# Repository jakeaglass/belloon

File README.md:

##Belloon &ndash; Bellarmine College Prep's High Altitude Balloon Project &ndash; Code, Schematics, and PCB Layout

Launching in ~~winter~~ summer of 2016 (targeting ~~January~~ June) to ~35km of altitude with a 1600g Hydrogen-filled latex balloon and a sensor package complete with the following:

- Camera (GoPro HERO))
- 144.390MHz APRS RadioMetrix Radio for telemetry
- GPS tracker (model TBD)
- ATMega CPU (with Arduino bootloader) with SD card for data logging
- Gas sensors (a sensor that can detect carbon-based gases and nitrous oxide, some of the worse pollutants in the atmosphere that also cause smog)
- Humidity Sensor
- Temperature Sensor

Once the balloon's payload&mdash;the board and sensors&mdash;is complete, we'll be able to launch and make use of the data collected to study environmental changes in the Earth’s atmosphere. Launch will be carried out with the help of the California Near Space Project, which has volunteered to facilitate the launch and retrieval. 

The board design is complete as of May 12 and has been sent off to be fabricated, so it will be debugged in person shortly. See the updated files for the full schematic and board (both done in EAGLE), gerber files, and BOM.

 &ndash; [Jake Glass](http://jake.glass) & [Mihir Trivedi](http://mihirtrivedi.com/)

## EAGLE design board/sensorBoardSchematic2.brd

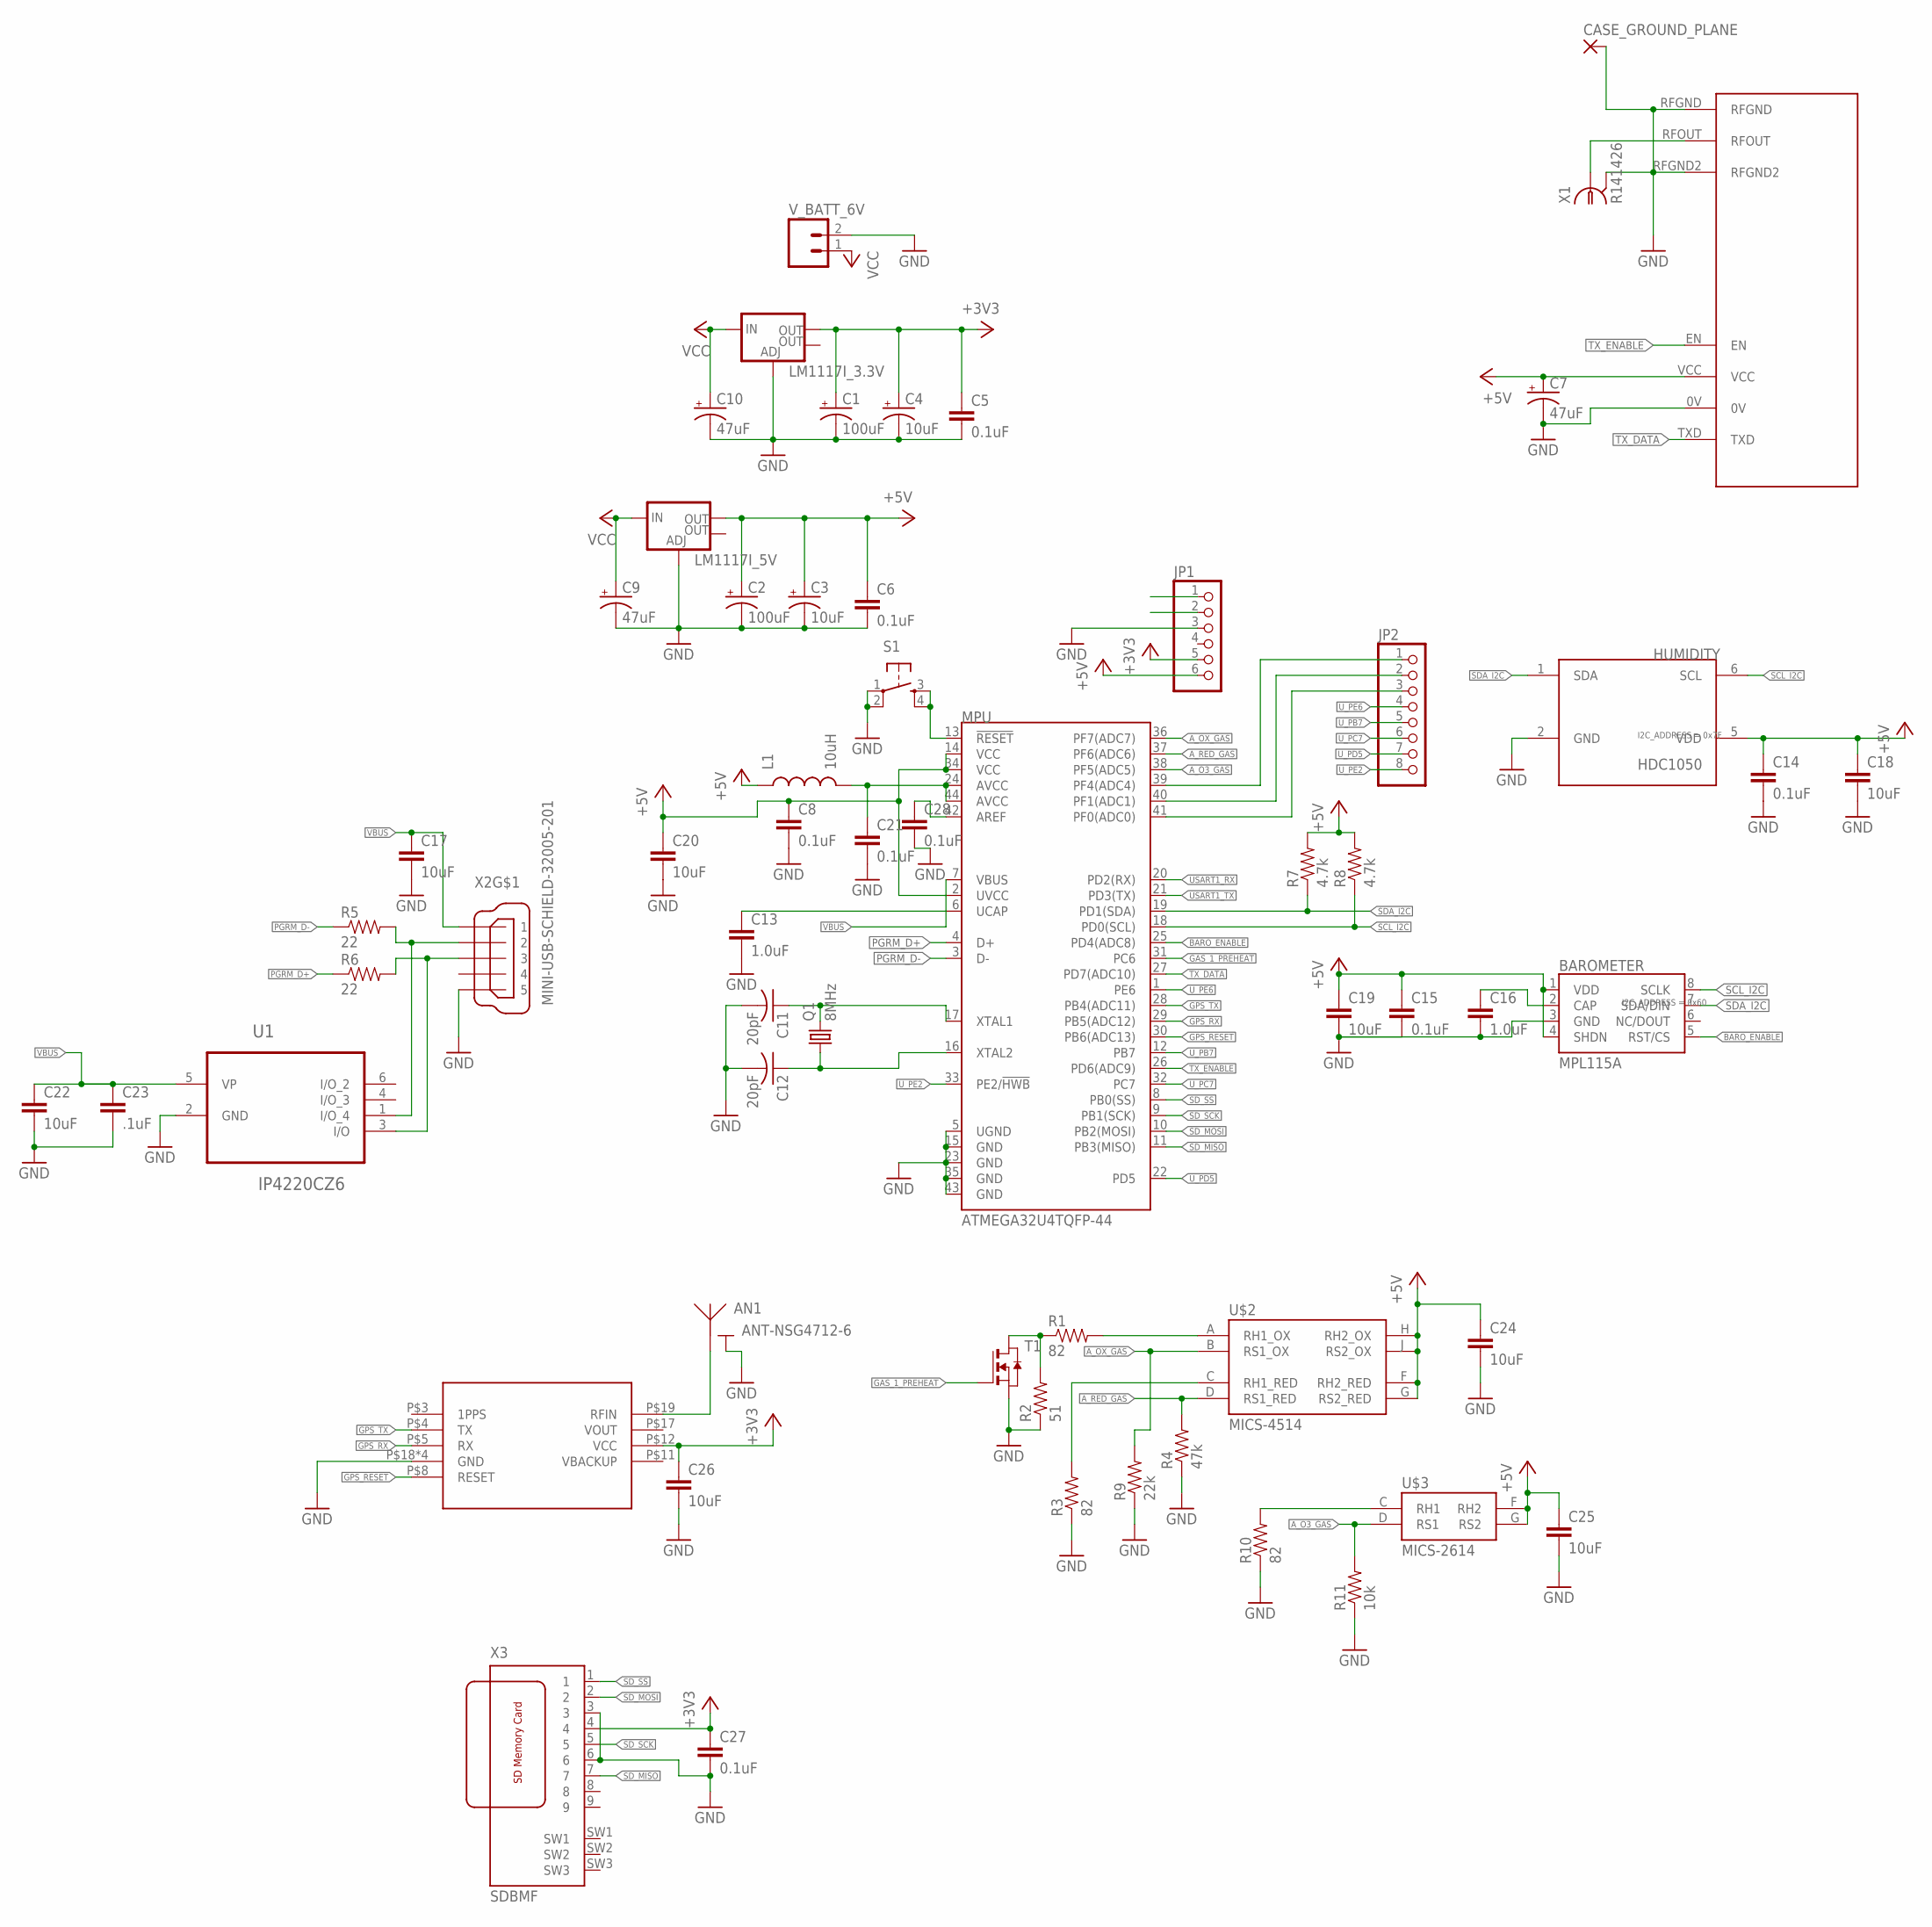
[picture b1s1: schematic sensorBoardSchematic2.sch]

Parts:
AN1: ANT-NSG4712-6
BAROMETER: MPL115A; LGA8
C1, C2: 100uF; EIA7343
C3, C4: 10uF; EIA3216
C5, C6, C27: 0.1uF; 0402-CAP
C7, C9, C10: 47uF; EIA3528
C8, C14, C15, C21, C28: 0.1uF; 0603-CAP
C11, C12: 20pF; C0402
C13, C16: 1.0uF; 0603-CAP
C17, C18, C19, C20, C22, C24, C25, C26: 10uF; 0603-CAP
C23: .1uF; 0603-CAP
CASE_GROUND_PLANE: 3,81/1,4
HUMIDITY: HDC1050; TI-S-PWSON-N6
IC1: RXM-GPS-FM; SMD-22
JP1: PINHD-1X6; 1X06
JP2: PINHD-1X8; 1X08
L1: 10uH; 1007
LM1117I_3.3V, LM1117I_5V: V_REG_LM1117SOT223; SOT223
MPU: ATMEGA32U4TQFP-44; TQFP44
Q1: 8MHz; HC49U70
R1, R3, R10: 82; 0402-RES
R2: 51; 0402-RES
R4: 47k; 0402-RES
R5, R6: 22; 0402-RES
R7, R8: 4.7k; 0402-RES
R9: 22k; 0402-RES
R11: 10k; 0402-RES
S1: TAC_SWITCHPTH; TACTILE-PTH
T1: NMOSSOT23; SOT-23
U1: IP4220CZ6; SOT95P275X110-6N
U$1: RADIOMETRIX-HX1
U$2: MICS-4514; MICS_10-SMD
U$3: MICS-2614; MICS_10-SMD
V_BATT_6V: M025MM; SCREWTERMINAL-5MM-2
X1: R141426
X2: MINI-USB-SCHIELD-32005-201; 32005-201
X3: SDBMF; SDBMF-009XXBXX2

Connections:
+3V3: C1.A (+), C4.A (+), C5.1, C26.1, C27.1, IC1.P$12 (VCC), JP1.5, LM1117I_3.3V.2 (OUT), X3.4
+5V: BAROMETER.1 (VDD), BAROMETER.4 (SHDN), C2.A (+), C3.A (+), C6.1, C7.A (+), C8.1, C14.1, C15.1, C18.1, C19.1, C20.1, C24.1, C25.1, HUMIDITY.5 (VDD), JP1.6, L1.1, LM1117I_5V.2 (OUT), MPU.2 (UVCC), MPU.14 (VCC), MPU.34 (VCC), R7.2, R8.2, U$1.VCC, U$2.F (RH2_RED), U$2.G (RS2_RED), U$2.H (RH2_OX), U$2.J (RS2_OX), U$3.F (RH2), U$3.G (RS2)
A_O3_GAS: MPU.38 (PF5(ADC5)), R11.2, U$3.D (RS1)
A_OX_GAS: MPU.36 (PF7(ADC7)), R9.2, U$2.B (RS1_OX)
A_RED_GAS: MPU.37 (PF6(ADC6)), R4.2, U$2.D (RS1_RED)
BARO_ENABLE: BAROMETER.5 (RST/CS), MPU.25 (PD4(ADC8))
GAS_1_PREHEAT: MPU.31 (PC6), T1.3 (G)
GND: AN1.G@1 (G), AN1.G@2 (G), AN1.G@3 (G), AN1.G@4 (G), AN1.G@5 (G), AN1.G@6 (G), AN1.G@7 (G), AN1.G@8 (G), AN1.G@9 (G), AN1.G@10 (G), BAROMETER.3 (GND), C1.C (-), C2.C (-), C3.C (-), C4.C (-), C5.2, C6.2, C7.C (-), C8.2, C9.C (-), C10.C (-), C11.2, C12.2, C13.2, C14.2, C15.2, C16.2, C17.2, C18.2, C19.2, C20.2, C21.2, C22.2, C23.2, C24.2, C25.2, C26.2, C27.2, C28.2, CASE_GROUND_PLANE.1, HUMIDITY.2 (GND), IC1.P$18 (GND), IC1.P$20 (GND), IC1.P$21 (GND), IC1.P$22 (GND), JP1.3, LM1117I_3.3V.1 (ADJ), LM1117I_5V.1 (ADJ), MPU.5 (UGND), MPU.15 (GND), MPU.23 (GND), MPU.35 (GND), MPU.43 (GND), R2.1, R3.1, R4.1, R9.1, R10.1, R11.1, S1.1, S1.2, T1.2 (S), U1.2 (GND), U$1.0V, U$1.RFGND, U$1.RFGND2, V_BATT_6V.2, X1.2, X1.3 (2), X1.4 (2), X1.5 (2), X2.5, X3.3, X3.6
GPS_RESET: IC1.P$8 (RESET), MPU.30 (PB6(ADC13))
GPS_RX: IC1.P$5 (RX), MPU.29 (PB5(ADC12))
GPS_TX: IC1.P$4 (TX), MPU.28 (PB4(ADC11))
unnamed: MPU.13 (!RESET), S1.3, S1.4
unnamed: U$1.RFOUT, X1.1
unnamed: AN1.A (ANT), IC1.P$19 (RFIN)
unnamed: C21.1, L1.2, MPU.24 (AVCC), MPU.44 (AVCC)
unnamed: R1.2, U$2.A (RH1_OX)
unnamed: C11.1, MPU.17 (XTAL1), Q1.2
unnamed: BAROMETER.2 (CAP), C16.1
unnamed: C12.1, MPU.16 (XTAL2), Q1.1
unnamed: R5.2, U1.1 (I/O_4), X2.2
unnamed: R6.2, U1.3 (I/O), X2.3
unnamed: C13.1, MPU.6 (UCAP)
unnamed: R1.1, R2.2, T1.1 (D)
unnamed: JP2.1, MPU.39 (PF4(ADC4))
unnamed: R10.2, U$3.C (RH1)
unnamed: JP2.2, MPU.40 (PF1(ADC1))
unnamed: JP2.3, MPU.41 (PF0(ADC0))
unnamed: R3.2, U$2.C (RH1_RED)
unnamed: C28.1, MPU.42 (AREF)
PGRM_D+: MPU.4 (D+), R6.1
PGRM_D-: MPU.3 (D-), R5.1
SCL_I2C: BAROMETER.8 (SCLK), HUMIDITY.6 (SCL), MPU.18 (PD0(SCL)), R8.1
SDA_I2C: BAROMETER.7 (SDA/DIN), HUMIDITY.1 (SDA), MPU.19 (PD1(SDA)), R7.1
SD_MISO: MPU.11 (PB3(MISO)), X3.7
SD_MOSI: MPU.10 (PB2(MOSI)), X3.2
SD_SCK: MPU.9 (PB1(SCK)), X3.5
SD_SS: MPU.8 (PB0(SS)), X3.1
TX_DATA: MPU.27 (PD7(ADC10)), U$1.TXD
TX_ENABLE: MPU.26 (PD6(ADC9)), U$1.EN
USART1_RX: JP1.1, MPU.20 (PD2(RX))
USART1_TX: JP1.2, MPU.21 (PD3(TX))
U_PB7: JP2.5, MPU.12 (PB7)
U_PC7: JP2.6, MPU.32 (PC7)
U_PD5: JP2.7, MPU.22 (PD5)
U_PE2: JP2.8, MPU.33 (PE2/!HWB)
U_PE6: JP2.4, MPU.1 (PE6)
VBUS: C17.1, C22.1, C23.1, MPU.7 (VBUS), U1.5 (VP)
VCC: C9.A (+), C10.A (+), LM1117I_3.3V.3 (IN), LM1117I_5V.3 (IN), V_BATT_6V.1

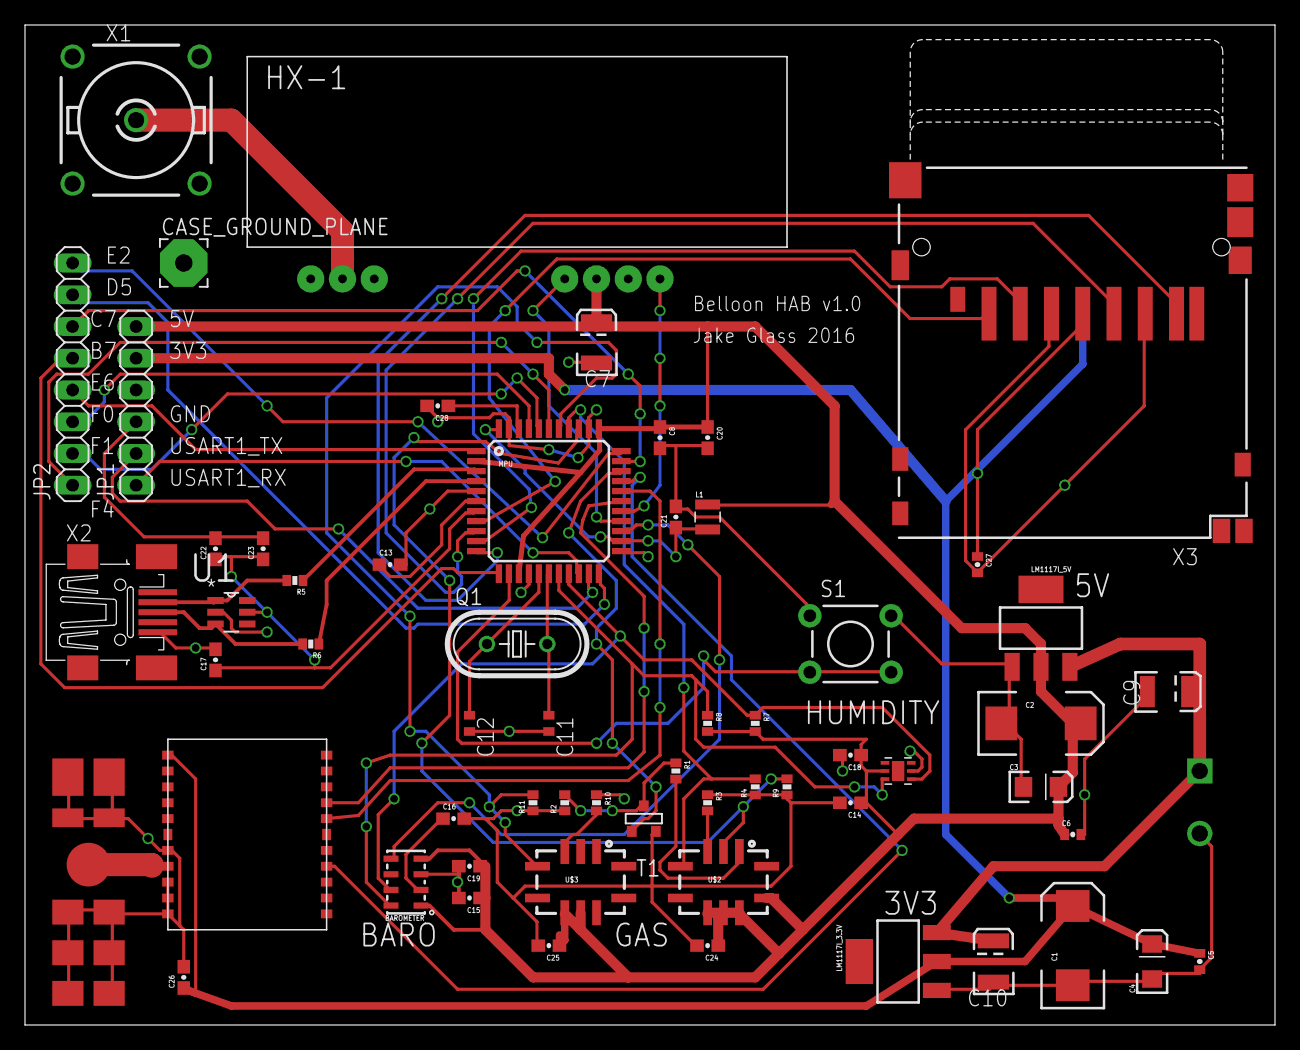
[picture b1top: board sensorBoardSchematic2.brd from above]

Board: 2 copper layers, 100.0 x 80.0 mm, 61 parts (1 on the bottom side), 48 nets.

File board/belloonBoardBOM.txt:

Partlist

Exported from sensorBoardSchematic2.brd at 5/11/2016 8:02 PM

EAGLE Version 7.5.0 Copyright (c) 1988-2015 CadSoft

Assembly variant: 

Part              Value             Package             Library                  Position (inch)       Orientation

AN1               ANT-NSG4712-6     ANT-NSG4712-6       roundsolutions           (0.2 0.45)            R0
BAROMETER         MPL115A           LGA8                SparkFun-Sensors         (1.2 0.45)            R180
C1                100uF             EIA7343             SparkFun-Capacitors      (3.3 0.25)            R90
C2                100uF             EIA7343             SparkFun-Capacitors      (3.2 0.95)            R0
C3                10uF              EIA3216             SparkFun-Retired         (3.2 0.75)            R0
C4                10uF              EIA3216             SparkFun-Retired         (3.55 0.2)            R90
C5                0.1uF             0402-CAP            SparkFun-Retired         (3.7 0.2)             R270
C6                0.1uF             0402-CAP            SparkFun-Retired         (3.3 0.6)             R0
C7                47uF              EIA3528             SparkFun-Capacitors      (1.8 2.15)            R90
C8                0.1uF             0603-CAP            SparkFun-Capacitors      (2 1.85)              R270
C9                47uF              EIA3528             SparkFun-Capacitors      (3.6 1.05)            R0
C10               47uF              EIA3528             SparkFun-Capacitors      (3.05 0.2)            R90
C11               20pF              C0402               resistor                 (1.65 0.95)           R270
C12               20pF              C0402               resistor                 (1.4 0.95)            R270
C13               1.0uF             0603-CAP            SparkFun-Capacitors      (1.15 1.45)           R0
C14               0.1uF             0603-CAP            SparkFun-Capacitors      (2.6 0.7)             R180
C15               0.1uF             0603-CAP            SparkFun-Capacitors      (1.4 0.4)             R180
C16               1.0uF             0603-CAP            SparkFun-Capacitors      (1.35 0.65)           R0
C17               10uF              0603-CAP            SparkFun-Capacitors      (0.6 1.15)            R90
C18               10uF              0603-CAP            SparkFun-Capacitors      (2.6 0.85)            R180
C19               10uF              0603-CAP            SparkFun-Capacitors      (1.4 0.5)             R180
C20               10uF              0603-CAP            SparkFun-Capacitors      (2.15 1.85)           R270
C21               0.1uF             0603-CAP            SparkFun-Capacitors      (2.05 1.6)            R90
C22               10uF              0603-CAP            SparkFun-Capacitors      (0.6 1.5)             R90
C23               .1uF              0603-CAP            SparkFun-Capacitors      (0.75 1.5)            R90
C24               10uF              0603-CAP            SparkFun-Capacitors      (2.15 0.25)           R180
C25               10uF              0603-CAP            SparkFun-Capacitors      (1.65 0.25)           R180
C26               10uF              0603-CAP            SparkFun-Capacitors      (0.5 0.15)            R90
C27               0.1uF             0402-CAP            SparkFun-Retired         (3 1.45)              R270
C28               0.1uF             0603-CAP            SparkFun-Capacitors      (1.3 1.95)            R180
CASE_GROUND_PLANE                   3,81/1,4            wirepad                  (0.5 2.4)             R0
HUMIDITY          HDC1050           TI-S-PWSON-N6       Ava                      (2.75 0.8)            R90
IC1               RXM-GPS-FM        SMD-22              linx-addl                (0.95 0.6)            R270
JP1                                 1X06                pinhead                  (0.35 1.95)           R90
JP2                                 1X08                pinhead                  (0.15 2.05)           R90
L1                10uH              1007                SparkFun-Passives        (2.15 1.6)            R0
LM1117I_3.3V                        SOT223              SparkFun-PowerIC         (2.75 0.2)            R90
LM1117I_5V                          SOT223              SparkFun-PowerIC         (3.2 1.25)            R0
MPU               ATMEGA32U4TQFP-44 TQFP44              SparkFun-DigitalIC       (1.65 1.65)           R0
Q1                8MHz              HC49U70             crystal                  (1.55 1.2)            R0
R1                82                0402-RES            SparkFun-Passives        (2.05 0.8)            R270
R2                51                0402-RES            SparkFun-Passives        (1.7 0.7)             R90
R3                82                0402-RES            SparkFun-Passives        (2.15 0.7)            R270
R4                47k               0402-RES            SparkFun-Passives        (2.3 0.75)            R90
R5                22                0402-RES            SparkFun-Passives        (0.85 1.4)            R180
R6                22                0402-RES            SparkFun-Passives        (0.9 1.2)             R180
R7                4.7k              0402-RES            SparkFun-Passives        (2.3 0.95)            R270
R8                4.7k              0402-RES            SparkFun-Passives        (2.15 0.95)           R270
R9                22k               0402-RES            SparkFun-Passives        (2.4 0.75)            R90
R10               82                0402-RES            SparkFun-Passives        (1.8 0.7)             R270
R11               10k               0402-RES            SparkFun-Passives        (1.6 0.7)             R90
S1                                  TACTILE-PTH         SparkFun-Retired         (2.6 1.2)             R0
T1                                  SOT-23              zetex                    (1.95 0.65)           R180
U$1               RADIOMETRIX-HX1   RADIOMETRIX-HX1     Ava                      (1.55 2.75)           R0
U$2               MICS-4514         MICS_10-SMD         SparkFun-Sensors         (2.2 0.45)            R0
U$3               MICS-2614         MICS_10-SMD         SparkFun-Sensors         (1.75 0.45)           R0
U1                                  SOT95P275X110-6N    NXP_By_element14_Batch_1 (0.65 1.3)            R0
V_BATT_6V                           SCREWTERMINAL-5MM-2 SparkFun-Connectors      (3.7 0.8)             MR270
X1                APRS_ANT          R141426             con-coax                 (0.35 2.85)           R0
X2                USB_PGRM          32005-201           con-cypressindustries    (0.3 1.3)             R0
X3                SDBMF             SDBMF-009XXBXX2     farnell                  (3.3 2.45)            R180

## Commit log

2015-11-24 initial commit of partially-complete sensor board
2015-11-24 newly descriptive readmen
2016-02-23 huge progress on sensor board schematic; configured USB, ESD isolation for USB, radio (note: need to figure out specs for digital packets from MPU), sensor IC's; analogue sensors and gas sensors need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
2016-02-23 ignoring dropbox
2016-02-23 ignoring Icon
2016-02-23 removing icon
2016-05-15 finished board v1, schematics and board layout, which should be sync'd up now
2016-05-15 updated readme for latest project changes

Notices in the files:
parts and their libraries:
SparkFun-Sensors: Licensing: Creative Commons ShareAlike 4.0 International - https://creativecommons.org/licenses/by-sa/4.0
